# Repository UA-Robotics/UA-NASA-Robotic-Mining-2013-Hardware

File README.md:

# UA-NASA-Robotic-Mining-2013-Hardware

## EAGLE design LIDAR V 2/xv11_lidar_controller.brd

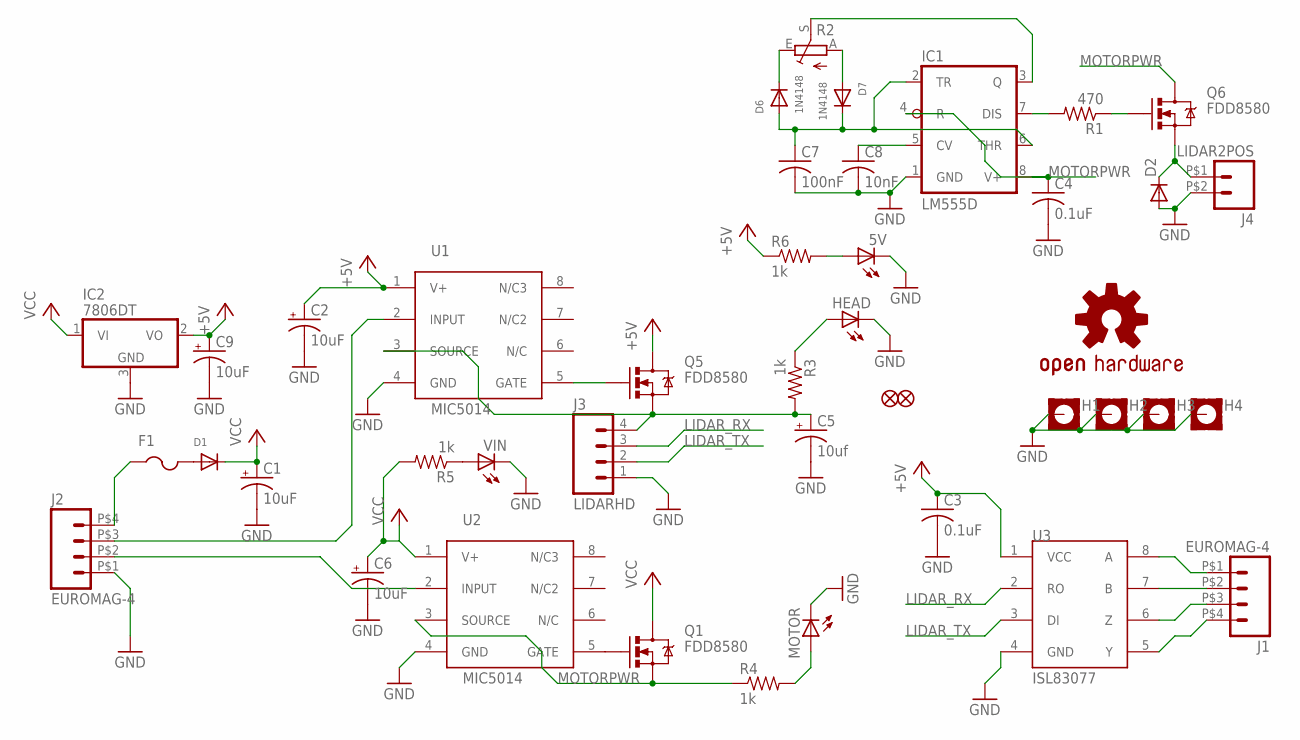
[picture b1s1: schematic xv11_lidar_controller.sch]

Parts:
5V: LEDCHIP-LED0805; CHIP-LED0805
C1, C2, C6, C9: 10uF; CT6032
C3, C4: 0.1uF; C0805
C5: 10uf; CT6032
C7: 100nF; C0805
C8: 10nF; C0805
D1: DIODESMA; SMADIODE
D2: DIODESMA; SMA-DIODE
D6, D7: 1N4148; SOD-323F
F1: PTCFUSE-1812; 1812
H1, H2, H3, H4: MOUNT-PAD-SQUARE5.5; 5,5-PAD-SQUARE
HEAD: LEDCHIP-LED0805; CHIP-LED0805
IC1: LM555D; SO08
IC2: 7806DT; TO252
J1, J2: EUROMAG-4; M4
J3: LIDARHD; 2MM4POS
J4: LIDAR2POS; 2MM2POS
JP1, JP2: FIDUCIAL1.5X3; FIDUCIAL-1.5X3
MOTOR: LEDCHIP-LED0805; CHIP-LED0805
Q1, Q5, Q6: FDD8580; DPAK
R1: 470; R0805
R2: TRIM_EU-B25P; B25P
R3, R4, R5, R6: 1k; 0805
U1, U2: MIC5014; SO08
U3: ISL83077; SO08
U$2: OSHW-LOGOL; OSHW-LOGO-L
VIN: LEDCHIP-LED0805; CHIP-LED0805

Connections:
+5V: C2.+, C3.1, C9.+, IC2.2 (VO), Q5.4 (D), R6.1, U1.1 (V+), U3.1 (VCC)
GND: 5V.C, C1.-, C2.-, C3.2, C4.2, C5.-, C6.-, C7.2, C8.2, C9.-, D2.A, H1.B5,5, H2.B5,5, H3.B5,5, H4.B5,5, HEAD.C, IC1.1 (GND), IC2.3 (GND), J2.P$1 (1), J3.1, J4.P$2 (2), MOTOR.C, U1.4 (GND), U2.4 (GND), U3.4 (GND), VIN.C
LIDAR_RX: J3.3, U3.2 (RO)
LIDAR_TX: J3.2, U3.3 (DI)
MOTORPWR: C4.1, IC1.4 (R), IC1.8 (V+), Q1.3 (S), Q6.4 (D), R4.1, U2.3 (SOURCE)
unnamed: C5.+, J3.4, Q5.3 (S), R3.2, U1.3 (SOURCE)
unnamed: J2.P$3 (3), U1.2 (INPUT)
unnamed: HEAD.A, R3.1
unnamed: R5.1, VIN.A
unnamed: Q5.1 (G), U1.5 (GATE)
unnamed: MOTOR.A, R4.2
unnamed: 5V.A, R6.2
unnamed: J2.P$2 (2), U2.2 (INPUT)
unnamed: J1.P$1 (1), U3.8 (A)
unnamed: D1.A, F1.2
unnamed: F1.1, J2.P$4 (4)
unnamed: C8.1, IC1.5 (CV)
unnamed: C7.1, D6.A, D7.C, IC1.2 (TR), IC1.6 (THR)
unnamed: D6.C, R2.E
unnamed: J1.P$2 (2), U3.7 (B)
unnamed: J1.P$3 (3), U3.6 (Z)
unnamed: J1.P$4 (4), U3.5 (Y)
unnamed: D7.A, R2.A
unnamed: IC1.3 (Q), R2.S
unnamed: IC1.7 (DIS), R1.2
unnamed: Q6.1 (G), R1.1
unnamed: D2.C, J4.P$1 (1), Q6.3 (S)
unnamed: Q1.1 (G), U2.5 (GATE)
VCC: C1.+, C6.+, D1.C, IC2.1 (VI), Q1.4 (D), R5.2, U2.1 (V+)

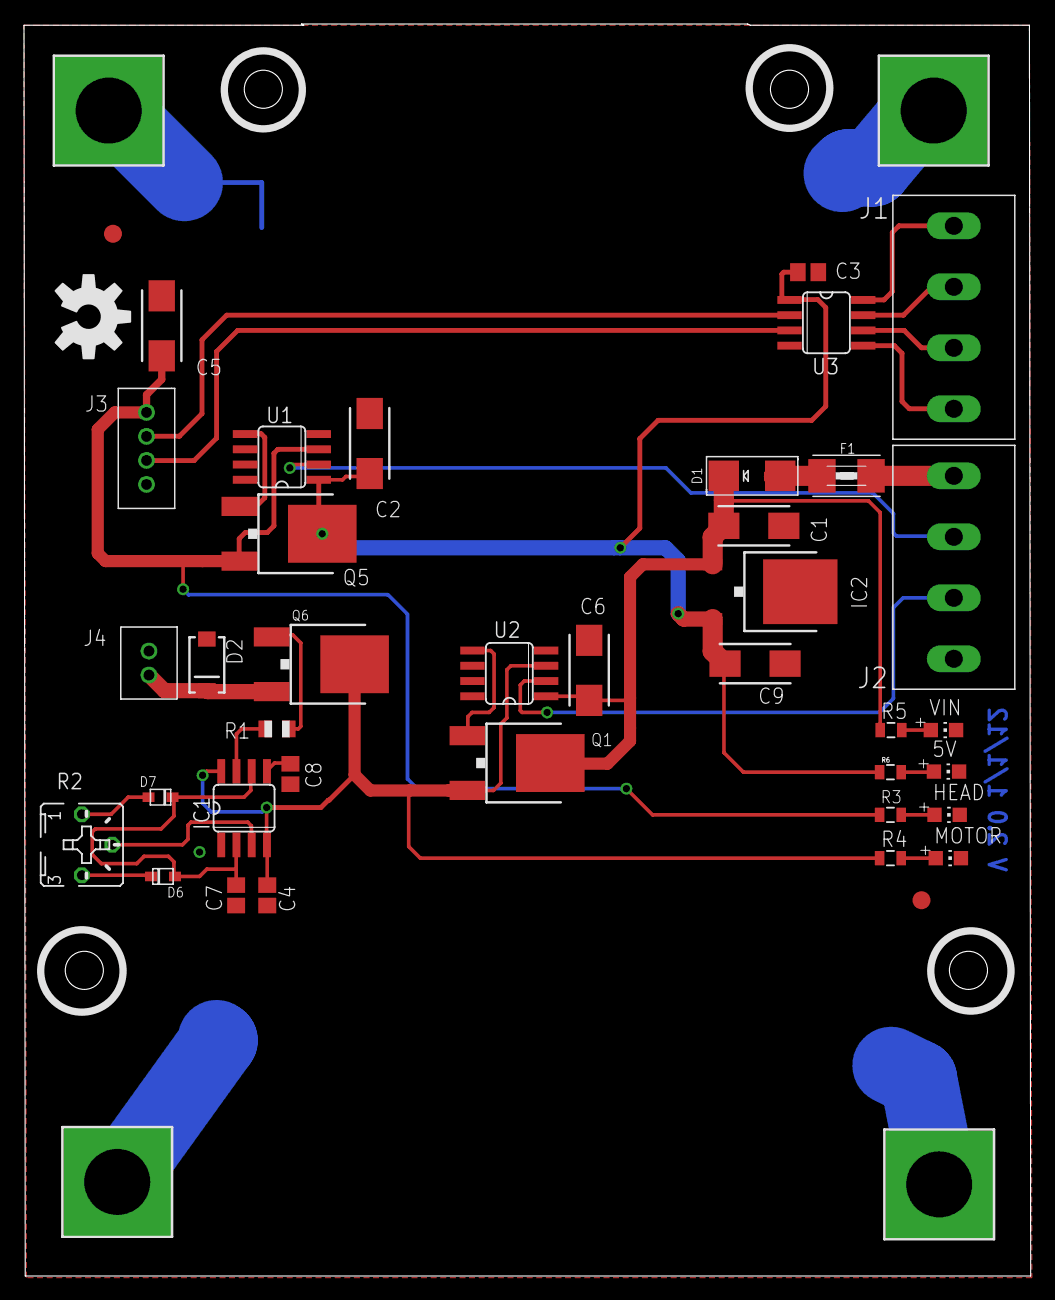
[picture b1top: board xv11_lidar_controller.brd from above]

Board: 2 copper layers, 83.9 x 104.3 mm, 43 parts (0 on the bottom side), 29 nets.

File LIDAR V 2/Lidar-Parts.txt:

Partlist

Exported from xv11_lidar_controller.sch at 1/16/2013 11:26:21 PM

EAGLE Version 6.2.0 Copyright (c) 1988-2012 CadSoft

Assembly variant: 

Part     Value          Device                 Package        Library  Sheet

5V                      LEDCHIP-LED0805        CHIP-LED0805   adafruit 1
C1       10uF           CPOL-USCT6032          CT6032         adafruit 1
C2       10uF           CPOL-USCT6032          CT6032         adafruit 1
C3       0.1uF          C-USC0805              C0805          adafruit 1
C4       0.1uF          C-USC0805              C0805          adafruit 1
C5       10uf           CPOL-USCT6032          CT6032         adafruit 1
C6       10uF           CPOL-USCT6032          CT6032         adafruit 1
C7       100nF          C-USC0805              C0805          adafruit 1
C8       10nF           C-USC0805              C0805          adafruit 1
C9       10uF           CPOL-USCT6032          CT6032         adafruit 1
D1                      DIODESMA               SMADIODE       adafruit 1
D2                      DIODESMA               SMA-DIODE      SparkFun 1
D6       1N4148         DIODESOD-323F          SOD-323F       adafruit 1
D7       1N4148         DIODESOD-323F          SOD-323F       adafruit 1
F1                      PTCFUSE-1812           1812           adafruit 1
H1                      MOUNT-PAD-SQUARE5.5    5,5-PAD-SQUARE holes    1
H2                      MOUNT-PAD-SQUARE5.5    5,5-PAD-SQUARE holes    1
H3                      MOUNT-PAD-SQUARE5.5    5,5-PAD-SQUARE holes    1
H4                      MOUNT-PAD-SQUARE5.5    5,5-PAD-SQUARE holes    1
HEAD                    LEDCHIP-LED0805        CHIP-LED0805   adafruit 1
IC1      LM555D         LM555D                 SO08           adafruit 1
IC2      7806DT         7806DT                 TO252          adafruit 1
J1       EUROMAG-4      EUROMAG-4              M4             NASA_LIB 1
J2       EUROMAG-4      EUROMAG-4              M4             NASA_LIB 1
J3       LIDARHD        LIDAR4POS              2MM4POS        NASA_LIB 1
J4       LIDAR2POS      LIDAR2POS              2MM2POS        NASA_LIB 1
MOTOR                   LEDCHIP-LED0805        CHIP-LED0805   adafruit 1
Q1       FDD8580        MOSFET-NCHANNELFDD8580 DPAK           SparkFun 1
Q5       FDD8580        MOSFET-NCHANNELFDD8580 DPAK           SparkFun 1
Q6       FDD8580        MOSFET-NCHANNELFDD8580 DPAK           SparkFun 1
R1       470            R-US_R0805             R0805          adafruit 1
R2                      TRIM_EU-B25P           B25P           pot      1
R3       1k             RESISTOR0805-RES       0805           SparkFun 1
R4       1k             RESISTOR0805-RES       0805           SparkFun 1
R5       1k             RESISTOR0805-RES       0805           SparkFun 1
R6       1k             RESISTOR0805-RES       0805           SparkFun 1
U1       MIC5014        MIC5014                SO08           NASA_LIB 1
U2       MIC5014        MIC5014                SO08           NASA_LIB 1
U6       SN65ALS180DR   SN65ALS180DR           SO14           NASA_LIB 1
VIN                     LEDCHIP-LED0805        CHIP-LED0805   adafruit 1

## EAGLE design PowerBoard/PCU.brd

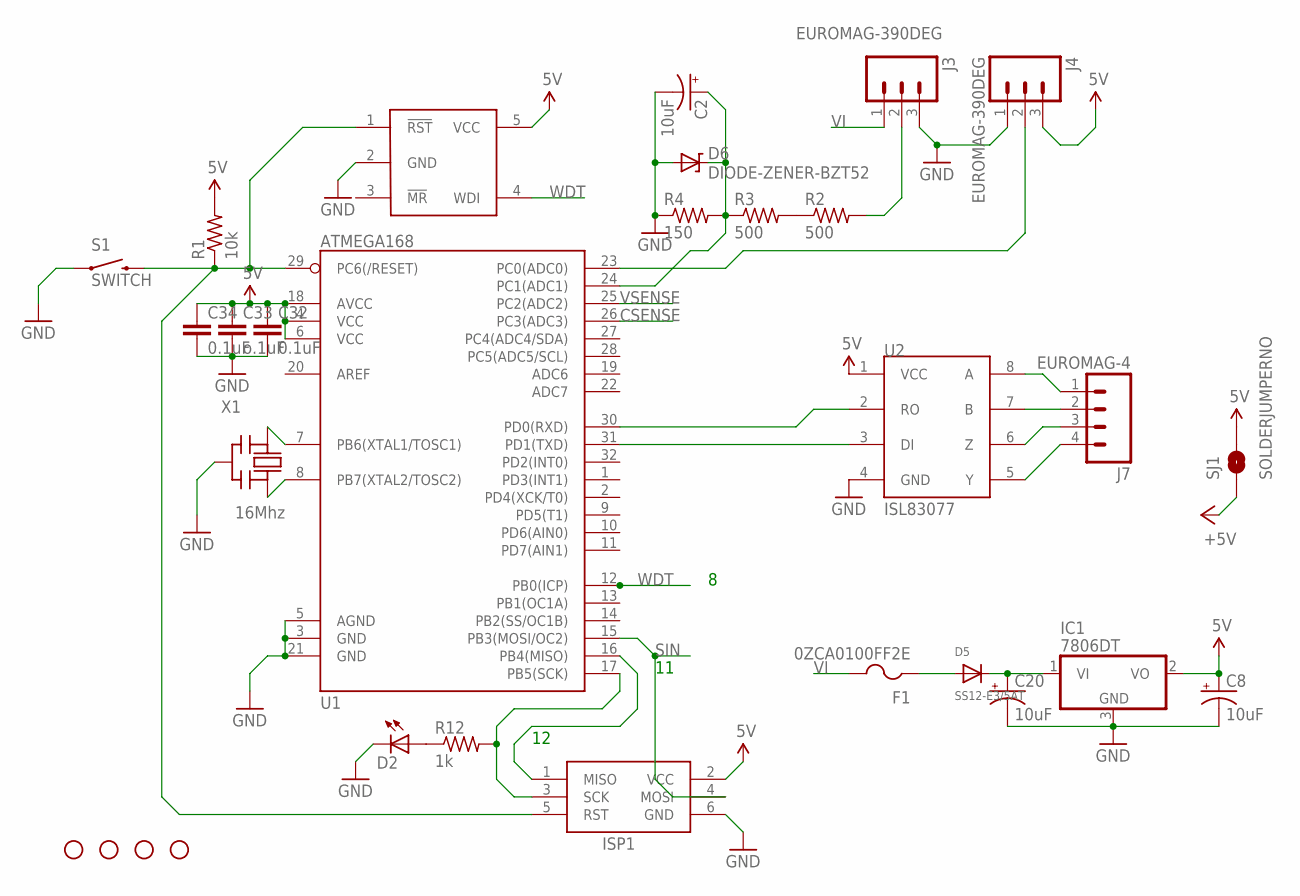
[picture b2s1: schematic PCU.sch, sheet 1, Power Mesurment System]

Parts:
C2: 10uF; EIA3216
C8, C20: 10uF; CT6032
C32, C34: 0.1uF; 0805
C33: o.1uF; 0805
D2: LEDCHIPLED_0805; CHIPLED_0805
D5: SS12-E3/5AT; SMADIODE
D6: DIODE-ZENER-BZT52; SOD-323
F1: 0ZCA0100FF2E; R1206
IC1: 7806DT; TO252
ISP1: AVRISP-6; AVRISP
J3, J4: EUROMAG-390DEG; M3
J7: EUROMAG-4; M4
JP1, JP3, JP4, JP5: STAND-OFF
R1: 10k; M0805
R2, R3: 500; M0805
R4: 150; M0805
R12: 1k; M0805
S1: SWITCH; TACTILE-PTH
SJ1: SOLDERJUMPERNO; SJ_2S-NO
U1: ATMEGA168; TQFP32-08
U2: ISL83077; SO08
U14: MAX823; SOT23-5L
X1: 16Mhz; AWCSR

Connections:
5V: C8.+, C32.1, C33.1, C34.1, IC1.2 (VO), ISP1.2 (VCC), J4.3, R1.2, SJ1.2, U1.4 (VCC), U1.6 (VCC), U1.18 (AVCC), U2.1 (VCC), U14.5 (VCC); also elsewhere on the board
+5V: SJ1.1; also elsewhere on the board
CSENSE: U1.26 (PC3(ADC3)); also elsewhere on the board
GND: C2.C (-), C8.-, C20.-, C32.2, C33.2, C34.2, D2.C, D6.2 (A), IC1.3 (GND), ISP1.6 (GND), J3.3, J4.1, R4.1, S1.1, U1.3 (GND), U1.5 (AGND), U1.21 (GND), U2.4 (GND), U14.2 (GND), X1.2 (GND); also elsewhere on the board
unnamed: J7.1, U2.8 (A)
unnamed: J7.2, U2.7 (B)
unnamed: J7.3, U2.6 (Z)
unnamed: ISP1.5 (RST), R1.1, S1.3 (2), U1.29 (PC6(/RESET)), U14.1 (!RST)
unnamed: U1.8 (PB7(XTAL2/TOSC2)), X1.3 (OUT)
unnamed: ISP1.1 (MISO), U1.16 (PB4(MISO))
unnamed: U1.7 (PB6(XTAL1/TOSC1)), X1.1 (IN)
unnamed: J7.4, U2.5 (Y)
unnamed: U1.30 (PD0(RXD)), U2.2 (RO)
unnamed: C20.+, D5.C, IC1.1 (VI)
unnamed: D2.A, R12.1
unnamed: J3.2, R2.2
unnamed: R2.1, R3.2
unnamed: C2.A (+), D6.1 (C), R3.1, R4.2, U1.24 (PC1(ADC1))
unnamed: J4.2, U1.23 (PC0(ADC0))
unnamed: D5.A, F1.1
unnamed: U1.31 (PD1(TXD)), U2.3 (DI)
SCLK: ISP1.3 (SCK), R12.2, U1.17 (PB5(SCK))
SIN: ISP1.4 (MOSI), U1.15 (PB3(MOSI/OC2))
VI: F1.2, J3.1
VSENSE: U1.25 (PC2(ADC2)); also elsewhere on the board
WDT: U1.12 (PB0(ICP)), U14.4 (WDI)

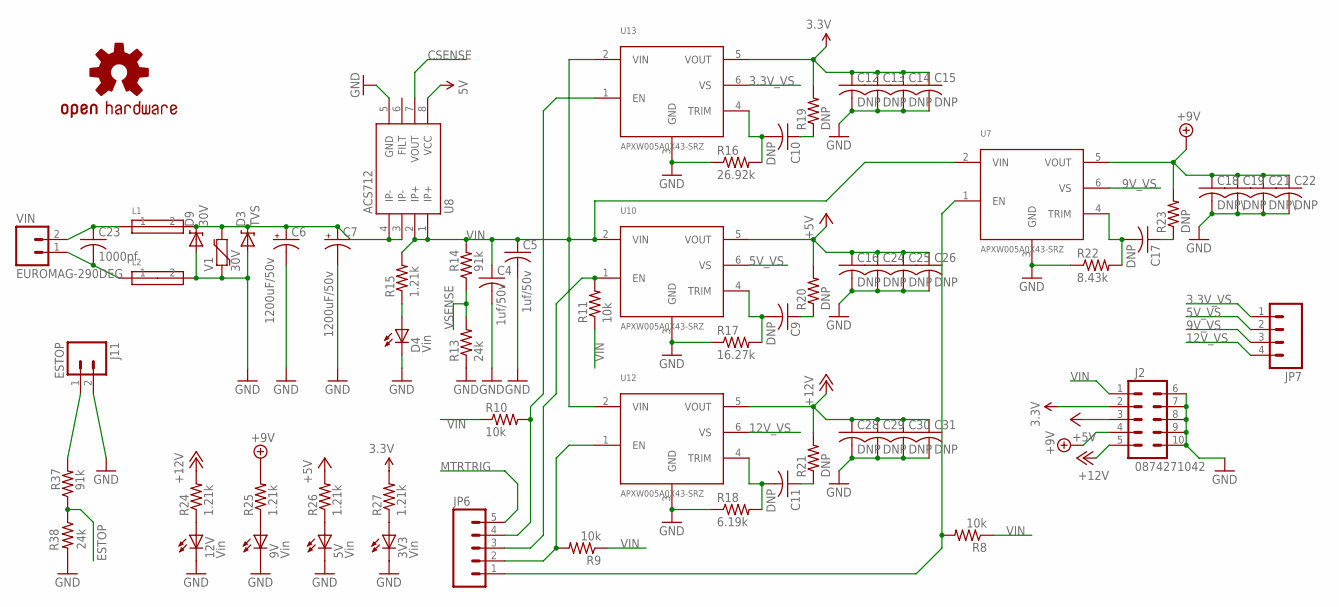
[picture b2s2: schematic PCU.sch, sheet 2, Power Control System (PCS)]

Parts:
3V3, 5V, 9V, 12V: Vin; CHIP-LED0805
C4, C5: 1uf/50v; C0805
C6, C7: 1200uF/50v; CAN_18MM
C9, C10, C11, C12, C13, C14, C15, C16, C17, C19, C22, C24, C25, C26, C28, C29, C30, C31: DNP; C0805
C18, C21: DNP\; C0805
C23: 1000pf; C1825
D3: TVS; DO-214AC
D4: Vin; CHIP-LED0805
D9: 30V; SMB-DIODE
J2: 0874271042
J11: ESTOP; M2
JP6: M05PTH_LONGPADS; 1X05_LONGPADS
JP7: M04POLAR; MOLEX-1X4
L1, L2: FERITEBEAD; 0603
R8, R9, R10, R11: 10k; R0805
R13, R38: 24k; R0805
R14, R37: 91k; R0805
R15, R24, R25, R26, R27: 1.21k; R0805
R16: 26.92k; R0805
R17: 16.27k; R0805
R18: 6.19k; R0805
R19, R20, R21, R23: DNP; R0805
R22: 8.43k; R0805
U7, U10, U12, U13: APXW005A0X43-SRZ
U8: ACS712; SO08
U$8: OSHW-LOGOM; OSHW-LOGO-M
V1: 30V; 0603-RES
VIN: EUROMAG-290DEG; M2

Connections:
3.3V: C12.1, C13.1, C14.1, C15.1, J2.2, R19.2, R27.2, U13.5 (VOUT)
3.3V_VS: JP7.1, U13.6 (VS)
5V: U8.8 (VCC); also elsewhere on the board
5V_VS: JP7.2, U10.6 (VS)
9V_VS: JP7.3, U7.6 (VS)
12V_VS: JP7.4, U12.6 (VS)
+5V: C16.1, C24.1, C25.1, C26.1, J2.3, R20.2, R26.2, U10.5 (VOUT); also elsewhere on the board
+9V: C18.1, C19.1, C21.1, C22.1, J2.4, R23.2, R25.2, U7.5 (VOUT)
+12V: C28.1, C29.1, C30.1, C31.1, J2.5, R21.2, R24.2, U12.5 (VOUT)
CSENSE: U8.7 (VOUT); also elsewhere on the board
ESTOP: R37.1, R38.1
GND: 3V3.C, 5V.C, 9V.C, 12V.C, C4.2, C5.2, C6.-, C7.-, C12.2, C13.2, C14.2, C15.2, C16.2, C18.2, C19.2, C21.2, C22.2, C24.2, C25.2, C26.2, C28.2, C29.2, C30.2, C31.2, D3.A, D4.C, D9.A, J2.6, J2.7, J2.8, J2.9, J2.10, J11.2, L2.2, R13.1, R16.1, R17.1, R18.1, R22.1, R38.2, U7.3 (GND), U8.5 (GND), U10.3 (GND), U12.3 (GND), U13.3 (GND), V1.1; also elsewhere on the board
MTRTRIG: JP6.5; also elsewhere on the board
unnamed: 12V.A, R24.1
unnamed: 9V.A, R25.1
unnamed: JP6.4, R10.2, U13.1 (EN)
unnamed: 5V.A, R26.1
unnamed: 3V3.A, R27.1
unnamed: JP6.3, R11.2, U10.1 (EN)
unnamed: JP6.2, R9.2, U12.1 (EN)
unnamed: JP6.1, R8.2, U7.1 (EN)
unnamed: C23.2, L2.1, VIN.1
unnamed: J11.1, R37.2
unnamed: C6.+, C7.+, D3.C, D9.C, L1.2, U8.3 (IP-), U8.4 (IP-), V1.2
unnamed: D4.A, R15.1
unnamed: C9.2, R17.2, U10.4 (TRIM)
unnamed: C10.2, R16.2, U13.4 (TRIM)
unnamed: C11.2, R18.2, U12.4 (TRIM)
unnamed: C10.1, R19.1
unnamed: C9.1, R20.1
unnamed: C11.1, R21.1
unnamed: C17.2, R22.2, U7.4 (TRIM)
unnamed: C17.1, R23.1
VIN: C4.1, C5.1, J2.1, R8.1, R9.1, R10.1, R11.1, R14.2, R15.2, U7.2 (VIN), U8.1 (IP+), U8.2 (IP+), U10.2 (VIN), U12.2 (VIN), U13.2 (VIN)
VOL: C23.1, L1.1, VIN.2
VSENSE: R13.2, R14.1; also elsewhere on the board

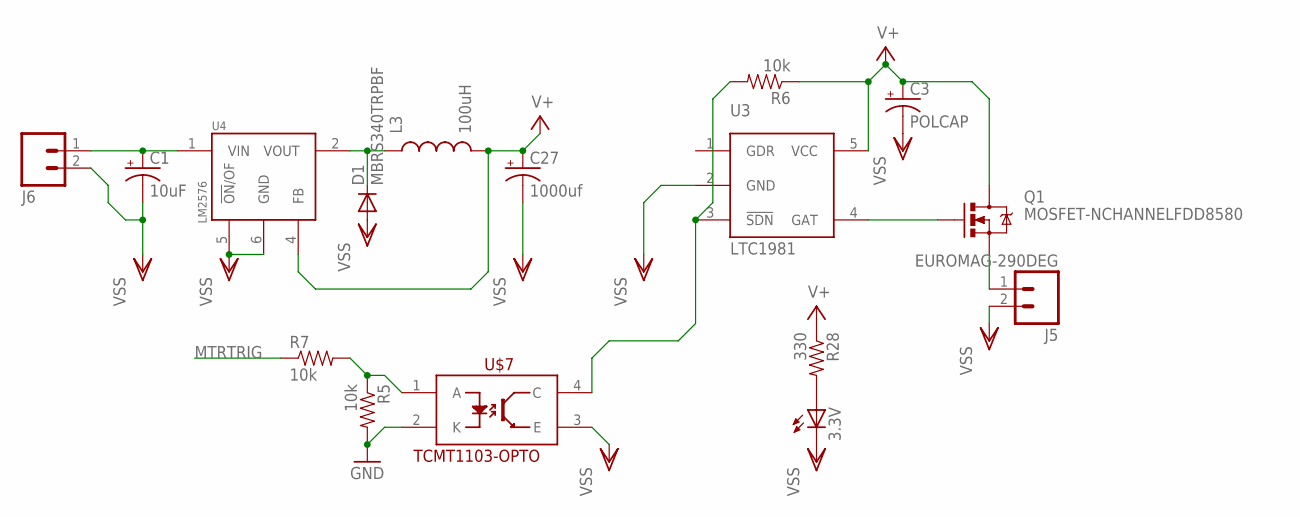
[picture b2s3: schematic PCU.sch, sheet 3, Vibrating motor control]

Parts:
3.3V: LEDCHIPLED_0805; CHIPLED_0805
C1: 10uF; EIA7343
C3: POLCAP; POLC1206
C27: 1000uf; PANASONIC_G
D1: MBRS340TRPBF; SMC
J5, J6: EUROMAG-290DEG; M2
L3: 100uH; INDUCTOR_5X3
Q1: MOSFET-NCHANNELFDD8580; DPAK
R5, R6, R7: 10k; 0805
R28: 330; 0805
U3: LTC1981; SOT23-5L
U4: LM2576; TO-263-5
U$7: TCMT1103-OPTO; SSOP-4

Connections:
GND: R5.2, U$7.2 (K); also elsewhere on the board
MTRTRIG: R7.1; also elsewhere on the board
unnamed: D1.C, L3.1, U4.2 (VOUT)
unnamed: Q1.1 (G), U3.4 (GAT)
unnamed: R6.2, U3.3 (!SDN), U$7.4 (C)
unnamed: J5.1, Q1.3 (S)
unnamed: R5.1, R7.2, U$7.1 (A)
unnamed: 3.3V.A, R28.2
V+: C3.1 (+), C27.+, L3.2, Q1.4 (D), R6.1, R28.1, U3.5 (VCC), U4.4 (FB)
VOLTIN: C1.A (+), J6.1, U4.1 (VIN)
VSS: 3.3V.C, C1.C (-), C3.2 (-), C27.-, D1.A, J5.2, J6.2, U3.2 (GND), U4.5 (!ON!/OF), U4.6 (GND), U$7.3 (E)

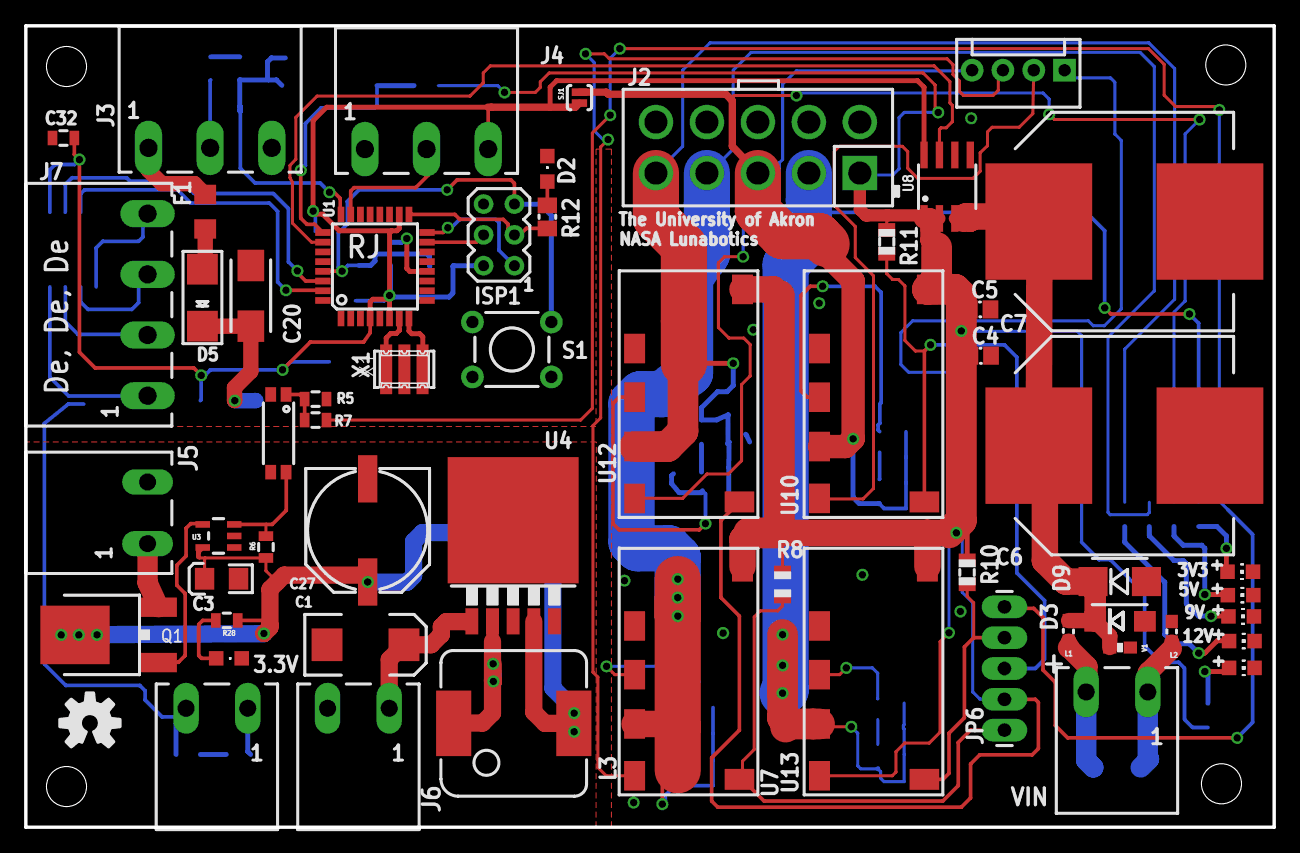
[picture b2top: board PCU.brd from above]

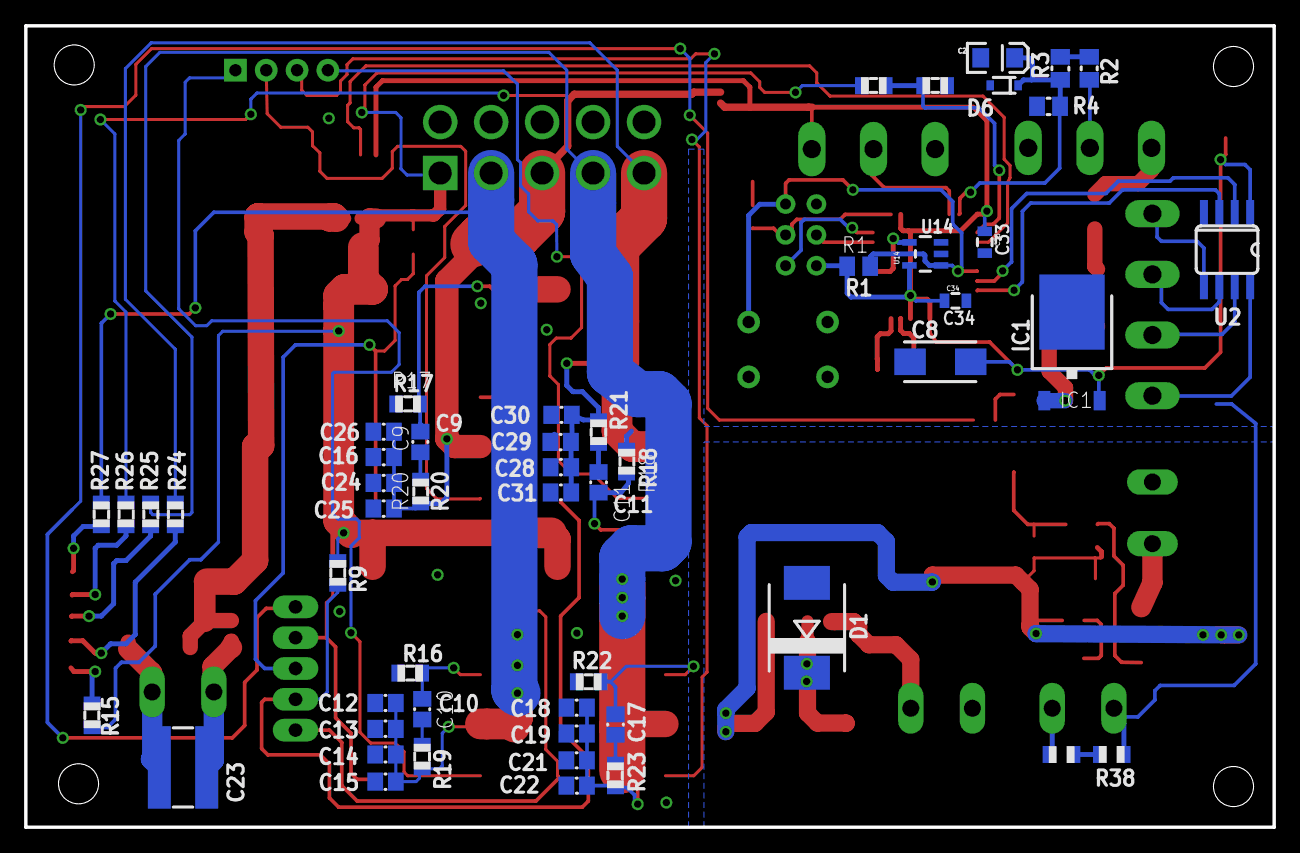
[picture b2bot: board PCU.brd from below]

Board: 2 copper layers, 102.9 x 66.0 mm, 113 parts (52 on the bottom side), 66 nets.

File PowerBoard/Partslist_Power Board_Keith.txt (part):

Partlist

Exported from PCU.brd at 4/19/2014 3:12:05 PM

EAGLE Version 6.5.0 Copyright (c) 1988-2013 CadSoft

Assembly variant: 

Part     Value                  Package          Library  Position (mil)        Orientation

3.3V                            CHIPLED_0805     adafruit (659 548)             R270
3V3      Vin                    CHIP-LED0805     adafruit (3940 829)            R270
5V       Vin                    CHIP-LED0805     adafruit (3941 753)            R270
9V       Vin                    CHIP-LED0805     adafruit (3943 684)            R270
12V      Vin                    CHIP-LED0805     adafruit (3945 604)            R270
C1       10uF                   EIA7343          SparkFun (1102 592)            R0
C2       10uF                   EIA3216          SparkFun (897 2496)            MR0
C3       POLCAP                 POLC1206         NASA_LIB (635 806)             R0
C4       1uf/50v                C0805            adafruit (3098 1530)           R0
C5       1uf/50v                C0805            adafruit (3096 1680)           R0
C6       1200uF/50v             CAN_18MM         NASA_LIB (3564 1238)           R180
C7       1200uF/50v             CAN_18MM         NASA_LIB (3564 1965)           R180
C8       10uF                   CT6032           adafruit (1083 1510)           MR0
C9       DNP                    C0805            adafruit (2770 1250)           MR90
C10      DNP                    C0805            adafruit (2764 383)            MR90
C11      DNP                    C0805            adafruit (2192 1119)           MR270
C12      DNP                    C0805            adafruit (2883 403)            MR180
C13      DNP                    C0805            adafruit (2883 319)            MR180
C14      DNP                    C0805            adafruit (2883 236)            MR180
C15      DNP                    C0805            adafruit (2883 148)            MR180
C16      DNP                    C0805            adafruit (2889 1201)           MR180
C17      DNP                    C0805            adafruit (2137 333)            MR90
C18      DNP\                   C0805            adafruit (2263 388)            MR180
C19      DNP                    C0805            adafruit (2263 304)            MR180
C20      10uF                   CT6032           adafruit (730 1724)            R270
C21      DNP\                   C0805            adafruit (2263 217)            MR180
C22      DNP                    C0805            adafruit (2263 135)            MR180
C23      1000pf                 C1825            adafruit (3540 194)            MR180
C24      DNP                    C0805            adafruit (2889 1117)           MR180
C25      DNP                    C0805            adafruit (2889 1034)           MR180
C26      DNP                    C0805            adafruit (2889 1283)           MR180
C27      1000uf                 PANASONIC_G      SparkFun (1109 963)            R270
C28      DNP                    C0805            adafruit (2314 1168)           MR180
C29      DNP                    C0805            adafruit (2315 1250)           MR180
C30      DNP                    C0805            adafruit (2312 1338)           MR180
C31      DNP                    C0805            adafruit (2314 1086)           MR180
C32      0.1uF                  0805             SparkFun (122 2236)            R180
C33      o.1uF                  0805             SparkFun (939 1898)            MR270
C34      0.1uF                  0805             SparkFun (1034 1708)           MR0
D1       MBRS340TRPBF           SMC              diode    (1516 647)            MR90
D2                              CHIPLED_0805     adafruit (1692 2136)           R0
D3       TVS                    DO-214AC         NASA_LIB (3550 668)            R0
D4       Vin                    CHIP-LED0805     adafruit (3945 517)            R270
D5       SS12-E3/5AT            SMADIODE         adafruit (573 1718)            R90
D6       DIODE-ZENER-BZT52      SOD-323          SparkFun (876 2407)            MR180
D9       30V                    SMB-DIODE        SparkFun (3549 797)            R0
F1       0ZCA0100FF2E           R1206            adafruit (582 1997)            R90
IC1      7806DT                 TO252            adafruit (656 1573)            MR0
ISP1     AVRISP-6               AVRISP           adafruit (1535.0999 1921.80007) R180
J2       0874271042             0874271042       NASA_LIB (2375 2205)           R0
J3       EUROMAG-390DEG         M3               NASA_LIB (598 2204)            R0
J4       EUROMAG-390DEG         M3               NASA_LIB (1300 2200)           R0
J5       EUROMAG-290DEG         M2               NASA_LIB (395 1020)            R90
J6       EUROMAG-290DEG         M2               NASA_LIB (1079 386)            R180
J7       EUROMAG-4              M4               NASA_LIB (395 1400)            R90
J11      ESTOP                  M2               NASA_LIB (620 386)             R180
JP6                             1X05_LONGPADS    SparkFun (3175 315)            R90
JP7                             MOLEX-1X4        SparkFun (3370 2456)           R180
L1                              0603             EmEndev  (3383 637)            R90
L2                              0603             EmEndev  (3718 634)            R90
L3       100uH                  INDUCTOR_5X3     NASA_LIB (1583 337)            R0
Q1       MOSFET-NCHANNELFDD8580 DPAK             SparkFun (222 624)             R90
R1       10k                    M0805            adafruit (1348.10002 1820)     MR180
R2       500                    M0805            adafruit (600 2462)            MR270
R3       500                    M0805            adafruit (694 2462)            MR90
R4       150                    M0805            adafruit (732 2339)            MR0
R5       10k                    0805             SparkFun (940 1389)            R0
R6       10k                    0805             SparkFun (779 909)             R90
R7       10k                    0805             SparkFun (940 1321)            R180
R8       10k                    R0805            adafruit (2455 788)            R270
R9       10k                    R0805            adafruit (3038 825)            MR270
R10      10k                    R0805            adafruit (3054 827)            R270
R11      10k                    R0805            adafruit (2793 1899)           R270
R12      1k                     M0805            adafruit (1692 1980)           R270
R13      24k                    R0805            adafruit (1100 2406)           MR180
R14      91k                    R0805            adafruit (1299 2406)           MR180
R15      1.21k                  R0805            adafruit (3835 363)            MR270
R16      26.92k                 R0805            adafruit (2803 500)            MR0
R17      16.27k                 R0805            adafruit (2810 1373)           MR0
R18      6.19k                  R0805            adafruit (2101 1186)           MR270
R19      DNP                    R0805            adafruit (2764 229)            MR270
R20      DNP                    R0805            adafruit (2769 1089)           MR270
R21      DNP                    R0805            adafruit (2192 1282)           MR90
R22      8.43k                  R0805            adafruit (2224 472)            MR0
R23      DNP                    R0805            adafruit (2137 168)            MR270
R24      1.21k                  R0805            adafruit (3565 1015)           MR90
R25      1.21k                  R0805            adafruit (3645 1015)           MR90
R26      1.21k                  R0805            adafruit (3725 1015)           MR90
R27      1.21k                  R0805            adafruit (3805 1015)           MR90
R28      330                    0805             SparkFun (652 671)             R180
R37      91k                    R0805            adafruit (690 236)             MR180
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
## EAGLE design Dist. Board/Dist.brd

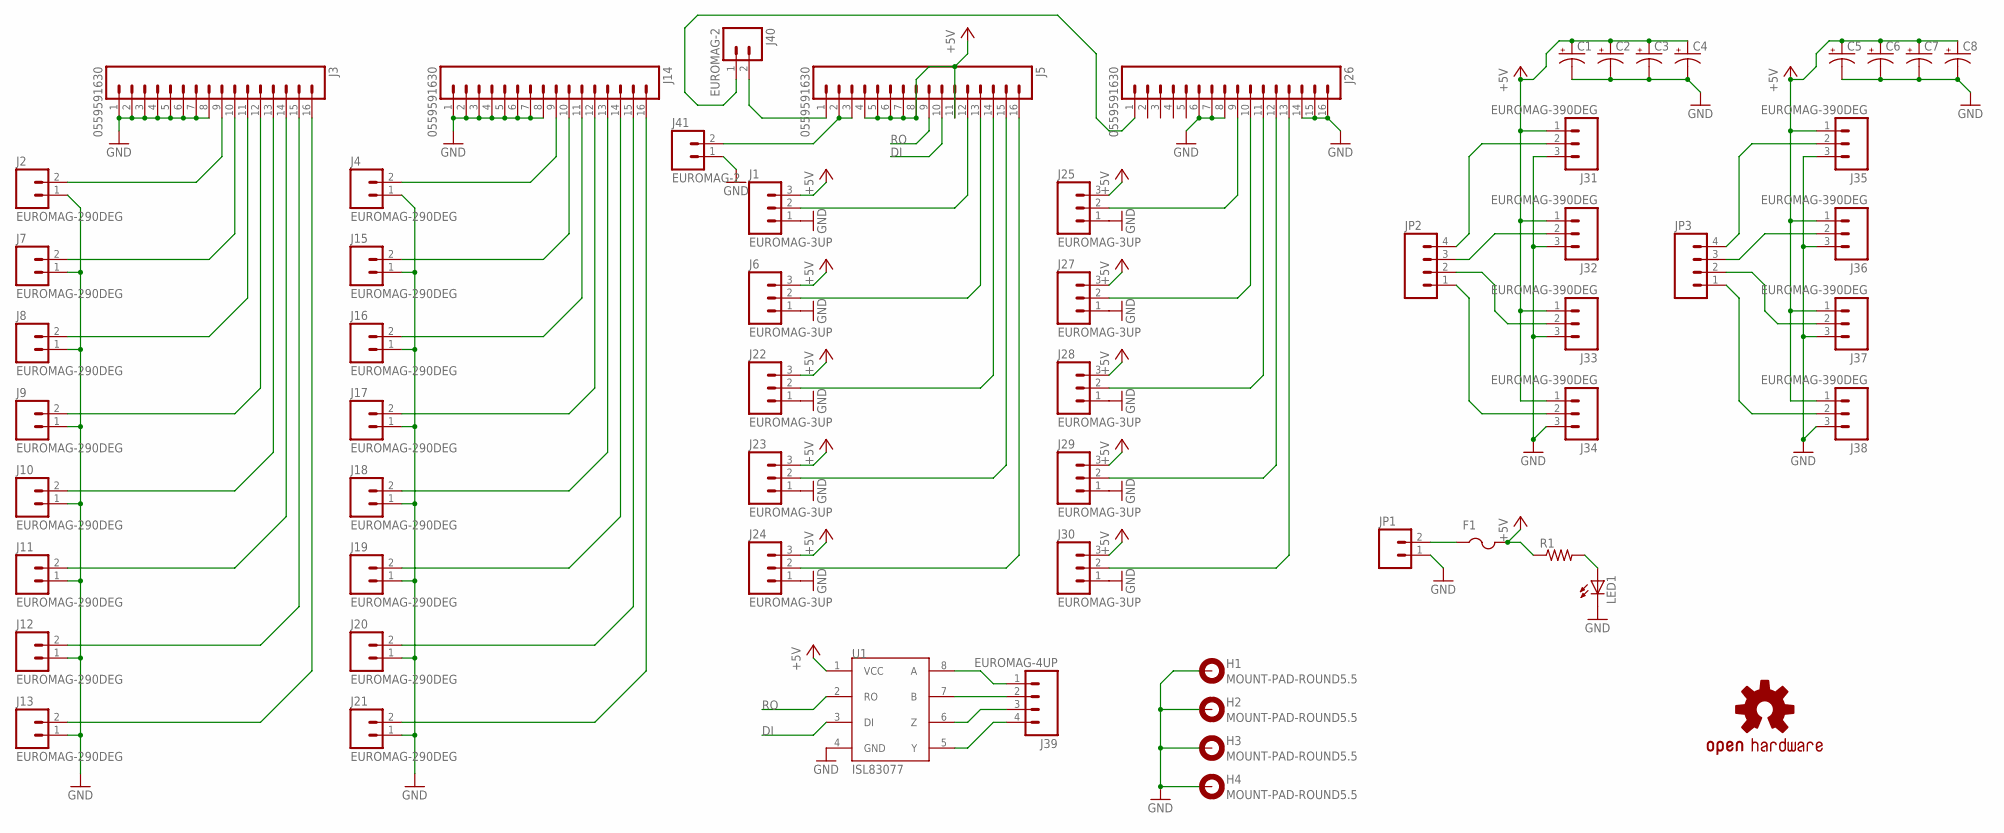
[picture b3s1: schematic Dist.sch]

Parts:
C1, C2, C3, C4, C5, C6, C7, C8: CAP_POL3528; EIA3528
F1: PTCFUSE-1812; 1812
H1, H2, H3, H4: MOUNT-PAD-ROUND5.5; 5,5-PAD
J1, J6, J22, J23, J24, J25, J27, J28, J29, J30: EUROMAG-3UP; M3-UP
J2, J4, J7, J8, J9, J10, J11, J12, J13, J15, J16, J17, J18, J19, J20, J21: EUROMAG-290DEG; M2
J3, J5, J14, J26: 0559591630
J31, J32, J33, J34, J35, J36, J37, J38: EUROMAG-390DEG; M3
J39: EUROMAG-4UP; M4-90
J40, J41: EUROMAG-2; M2-UP
JP1: M02POLAR_LOCK; MOLEX-1X2_LOCK
JP2, JP3: M04POLAR_LOCK; MOLEX-1X4_LOCK
LED1: LEDCHIPLED_0805; CHIPLED_0805
R1: R-US_R0805; R0805
U1: ISL83077; SO08
U$1: OSHW-LOGOL; OSHW-LOGO-L

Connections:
+5V: C1.A (+), C2.A (+), C3.A (+), C4.A (+), C5.A (+), C6.A (+), C7.A (+), C8.A (+), F1.2, J1.3, J5.4, J5.5, J5.6, J5.7, J5.8, J5.11, J6.3, J22.3, J23.3, J24.3, J25.3, J27.3, J28.3, J29.3, J30.3, J31.1, J32.1, J33.1, J34.1, J35.1, J36.1, J37.1, J38.1, R1.1, U1.1 (VCC)
DI: J5.10, U1.3 (DI)
GND: C1.C (-), C2.C (-), C3.C (-), C4.C (-), C5.C (-), C6.C (-), C7.C (-), C8.C (-), H1.B5,5, H2.B5,5, H3.B5,5, H4.B5,5, J1.1, J2.1, J3.1, J3.2, J3.3, J3.4, J3.5, J3.6, J3.7, J3.8, J4.1, J6.1, J7.1, J8.1, J9.1, J10.1, J11.1, J12.1, J13.1, J14.1, J14.2, J14.3, J14.4, J14.5, J14.6, J14.7, J14.8, J15.1, J16.1, J17.1, J18.1, J19.1, J20.1, J21.1, J22.1, J23.1, J24.1, J25.1, J26.6, J26.7, J26.8, J26.14, J26.15, J26.16, J27.1, J28.1, J29.1, J30.1, J31.3, J32.3, J33.3, J34.3, J35.3, J36.3, J37.3, J38.3, J41.1, JP1.1, LED1.C, U1.4 (GND)
unnamed: J2.2, J3.9
unnamed: J3.10, J7.2
unnamed: J3.11, J8.2
unnamed: J3.12, J9.2
unnamed: J3.13, J10.2
unnamed: J3.14, J11.2
unnamed: J3.15, J12.2
unnamed: J3.16, J13.2
unnamed: J25.2, J26.9
unnamed: J4.2, J14.9
unnamed: J14.10, J15.2
unnamed: J14.11, J16.2
unnamed: J14.12, J17.2
unnamed: J14.13, J18.2
unnamed: J14.14, J19.2
unnamed: J14.15, J20.2
unnamed: J14.16, J21.2
unnamed: J26.10, J27.2
unnamed: J26.11, J28.2
unnamed: J26.12, J29.2
unnamed: J26.13, J30.2
unnamed: J1.2, J5.12
unnamed: J5.13, J6.2
unnamed: J5.14, J22.2
unnamed: J5.15, J23.2
unnamed: J5.16, J24.2
unnamed: J5.2, J5.3, J41.2
unnamed: J5.1, J40.2
unnamed: J26.1, J40.1
unnamed: J39.1, U1.8 (A)
unnamed: J39.2, U1.7 (B)
unnamed: J39.3, U1.6 (Z)
unnamed: J39.4, U1.5 (Y)
unnamed: J31.2, JP2.4
unnamed: J32.2, JP2.3
unnamed: J33.2, JP2.2
unnamed: J34.2, JP2.1
unnamed: F1.1, JP1.2
unnamed: J35.2, JP3.4
unnamed: J36.2, JP3.3
unnamed: J37.2, JP3.2
unnamed: J38.2, JP3.1
unnamed: LED1.A, R1.2
RO: J5.9, U1.2 (RO)

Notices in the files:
parts and their libraries:
SparkFun: Licensing: CC v3.0 Share-Alike You are welcome to use this library for commercial purposes.
